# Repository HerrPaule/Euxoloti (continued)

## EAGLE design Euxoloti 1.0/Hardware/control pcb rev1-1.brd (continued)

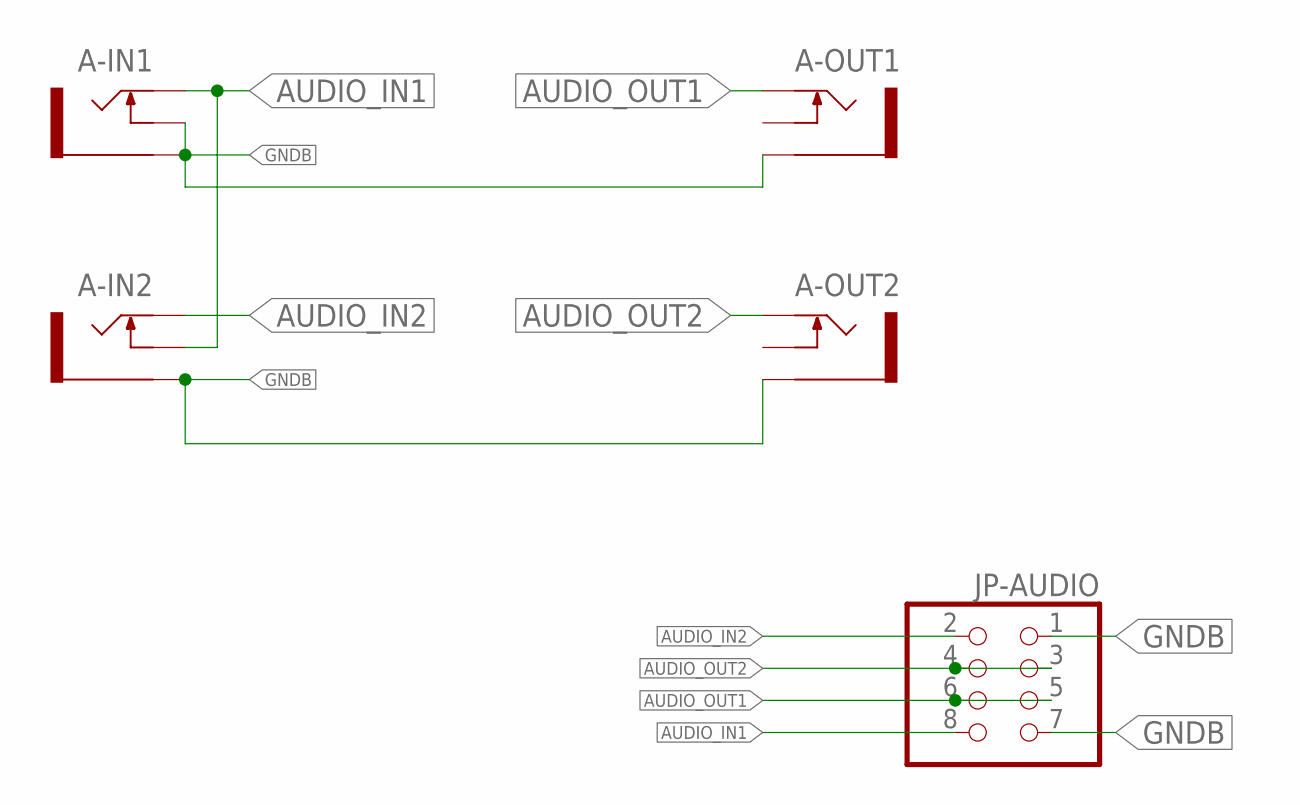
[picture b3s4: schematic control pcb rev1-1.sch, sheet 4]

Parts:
A-IN1, A-IN2: THONKICONNNEW; WQP-PJ301M-12_JACK
A-OUT1, A-OUT2: THONKICONNNEW; WQP-PJ301M-12_JACK
JP-AUDIO: PINHD-2X4_2.54; 2X04

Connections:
AUDIO_IN1: A-IN1.P$1_TIP (TIP), A-IN2.P$2_SWITCH (SWITCH), JP-AUDIO.8
AUDIO_IN2: A-IN2.P$1_TIP (TIP), JP-AUDIO.2
AUDIO_OUT1: A-OUT1.P$1_TIP (TIP), JP-AUDIO.5, JP-AUDIO.6
AUDIO_OUT2: A-OUT2.P$1_TIP (TIP), JP-AUDIO.3, JP-AUDIO.4
GNDB: A-IN1.P$2_SWITCH (SWITCH), A-IN1.P$3_SLEEVE (SLEEVE), A-IN2.P$3_SLEEVE (SLEEVE), A-OUT1.P$3_SLEEVE (SLEEVE), A-OUT2.P$3_SLEEVE (SLEEVE), JP-AUDIO.1, JP-AUDIO.7

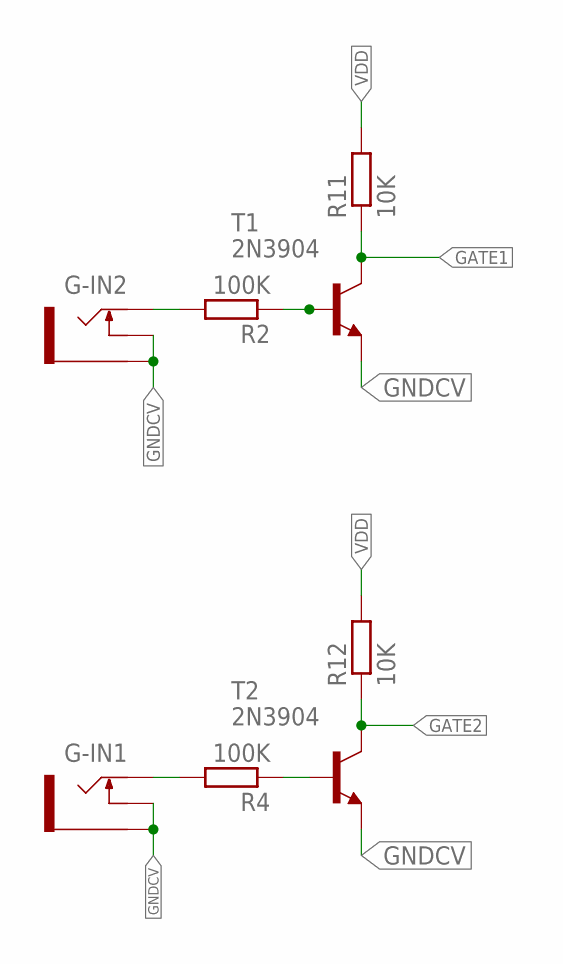
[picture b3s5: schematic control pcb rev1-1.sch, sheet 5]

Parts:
G-IN1, G-IN2: THONKICONNNEW; WQP-PJ301M-12_JACK
R2, R4: 100K; 0207/7
R11, R12: 10K; 0207/7
T1, T2: 2N3904; TO92

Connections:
GATE1: R11.1, T1.1 (C); also elsewhere on the board
GATE2: R12.1, T2.1 (C); also elsewhere on the board
GNDCV: G-IN1.P$2_SWITCH (SWITCH), G-IN1.P$3_SLEEVE (SLEEVE), G-IN2.P$2_SWITCH (SWITCH), G-IN2.P$3_SLEEVE (SLEEVE), T1.3 (E), T2.3 (E); also elsewhere on the board
unnamed: G-IN2.P$1_TIP (TIP), R2.2
unnamed: G-IN1.P$1_TIP (TIP), R4.2
unnamed: R2.1, T1.2 (B)
unnamed: R4.1, T2.2 (B)
VDD: R11.2, R12.2; also elsewhere on the board

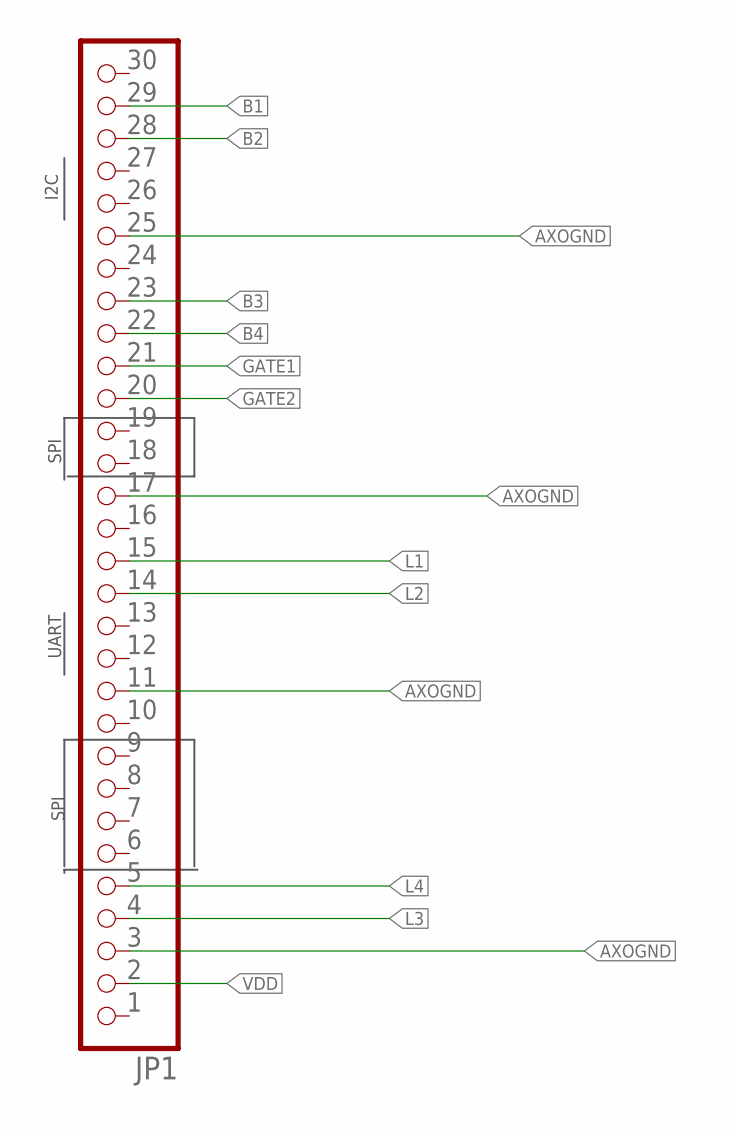
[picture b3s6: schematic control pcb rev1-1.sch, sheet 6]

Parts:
JP1: PINHD-1X30; 1X30

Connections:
AXOGND: JP1.3, JP1.11, JP1.17, JP1.25; also elsewhere on the board
B1: JP1.29; also elsewhere on the board
B2: JP1.28; also elsewhere on the board
B3: JP1.23; also elsewhere on the board
B4: JP1.22; also elsewhere on the board
GATE1: JP1.21; also elsewhere on the board
GATE2: JP1.20; also elsewhere on the board
L1: JP1.15; also elsewhere on the board
L2: JP1.14; also elsewhere on the board
L3: JP1.4; also elsewhere on the board
L4: JP1.5; also elsewhere on the board
VDD: JP1.2; also elsewhere on the board

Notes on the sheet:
SPI
UART
I2C

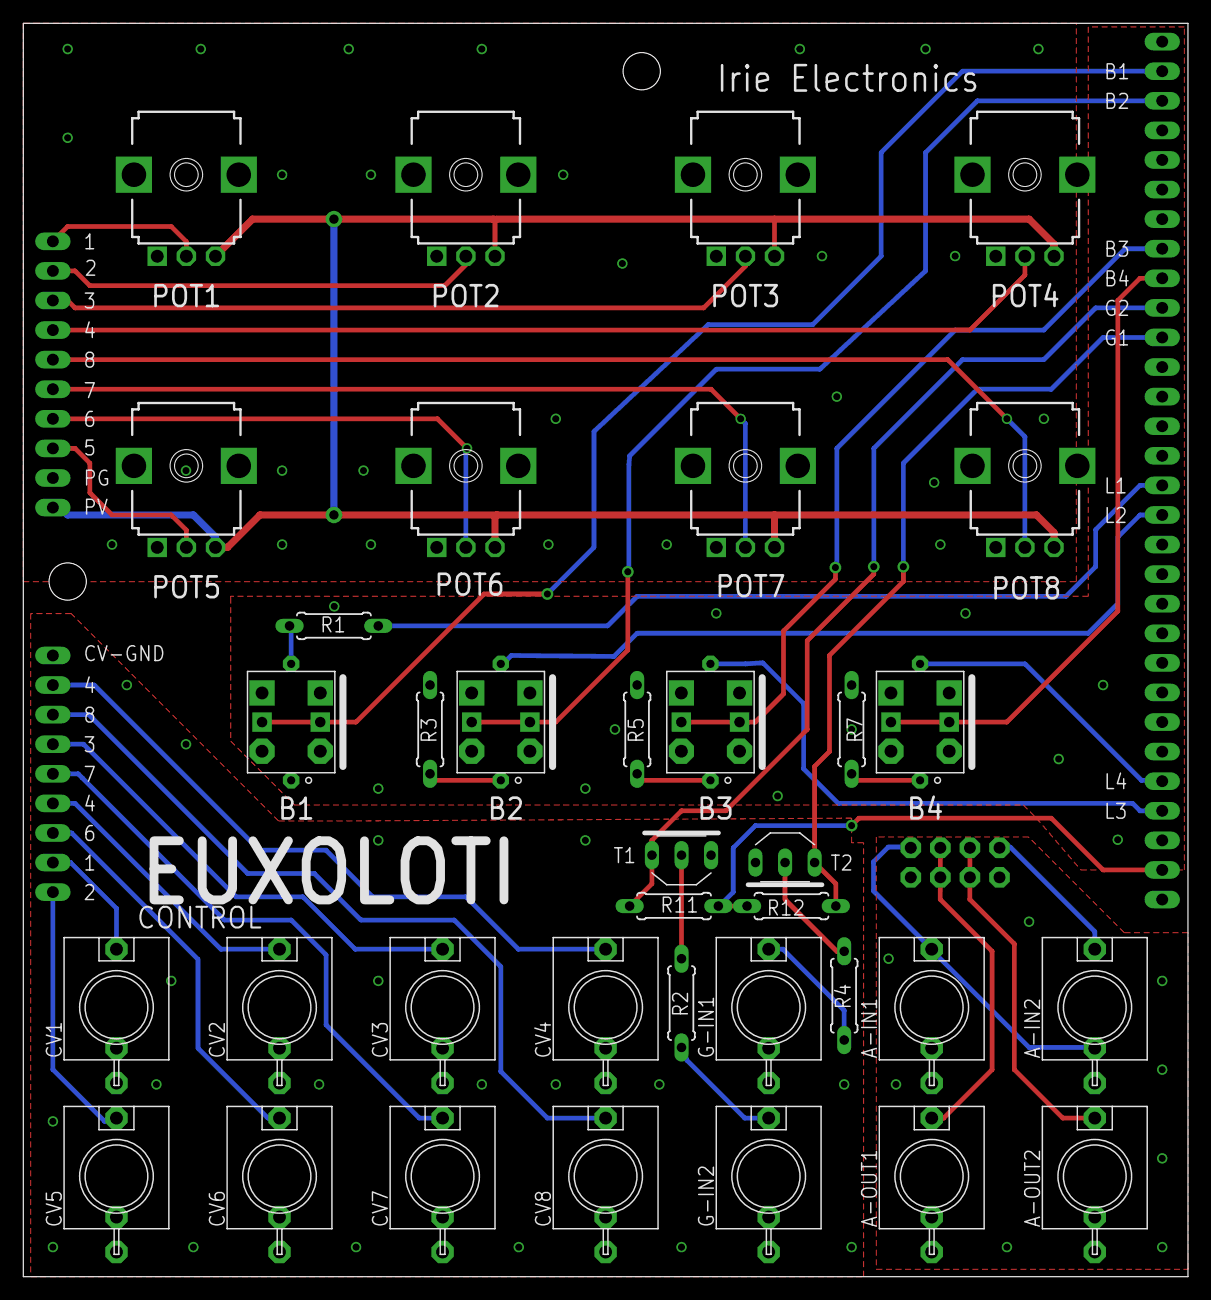
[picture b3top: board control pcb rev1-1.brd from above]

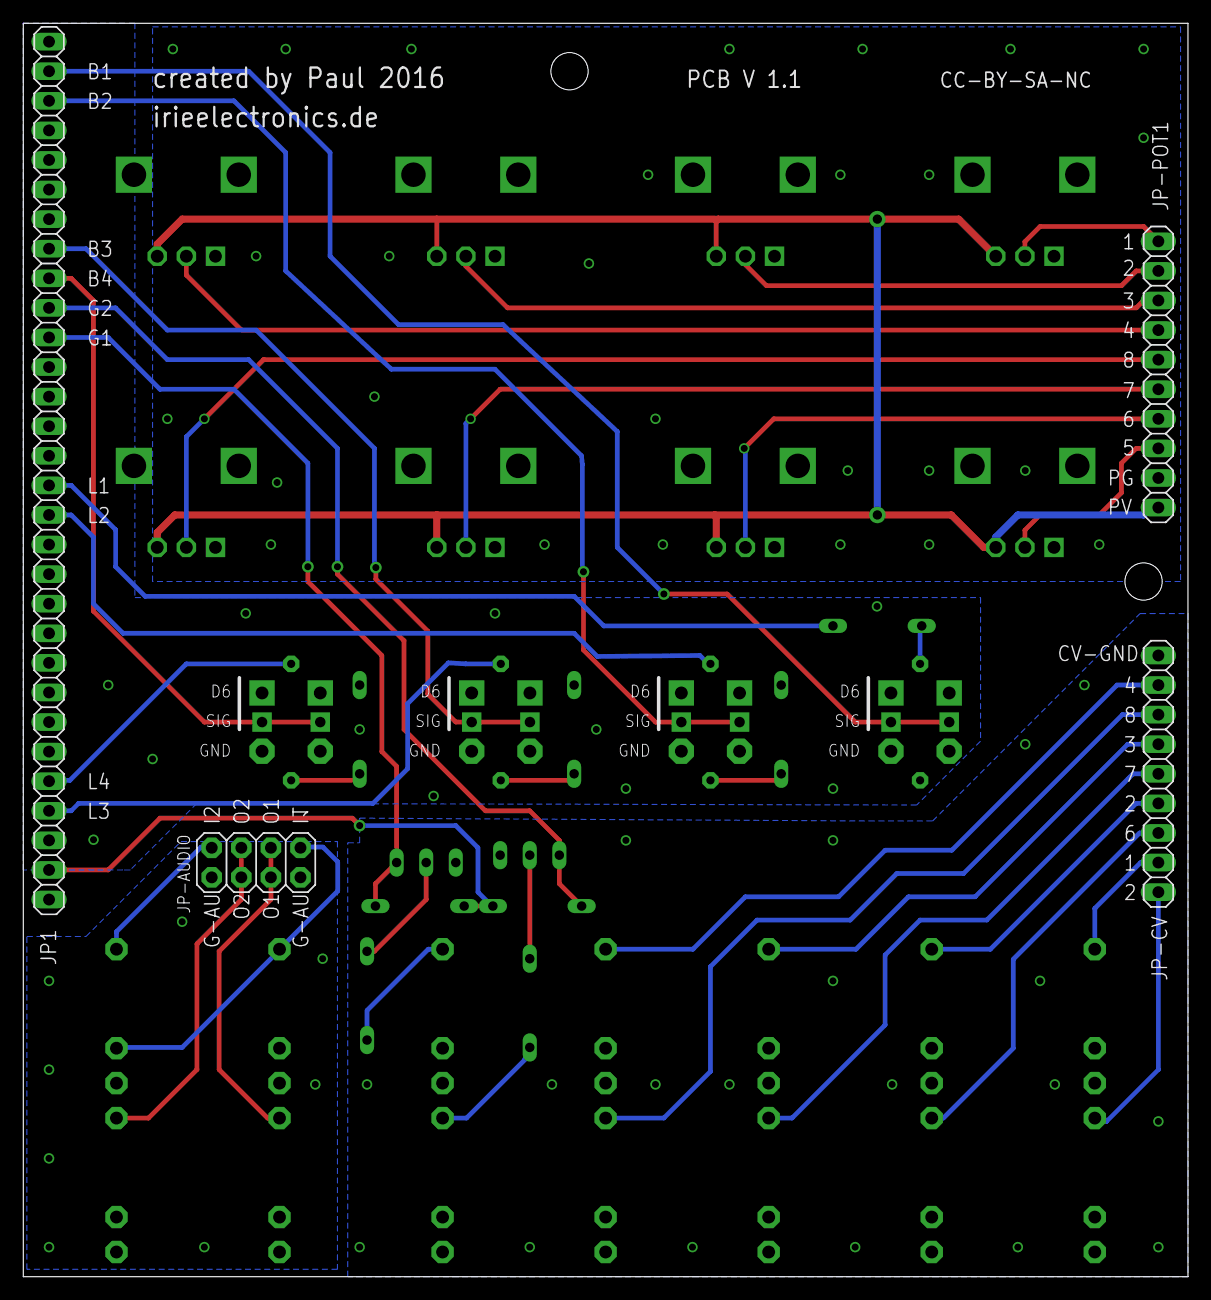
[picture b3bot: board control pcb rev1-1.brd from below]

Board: 4 copper layers, 100.0 x 107.6 mm, 40 parts (4 on the bottom side), 44 nets.

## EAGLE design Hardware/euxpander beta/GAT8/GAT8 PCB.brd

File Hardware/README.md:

##### Changelog

####### Core PCB Version 1.1:
- error correction 
- some components are rearranged or deleted
- Analog ground for ADCs, POTs and AUDIO
- better heat management for Vreg (PCB can be used as heat sink or a heatsink for TO-220)
- CS pins from ADCs are connected to other Axo pinouts
- detailed labels for pin outs and used pins.
- connections to connect upcoming "GAT8" and "USB2MCV" extensions. 
- optional use of lin/rin pins for audio directly or normalize the Eurorack signal by a big audio jack to the audio input header behind Axo's audio in jack. so you can use mics etc. like normal with Axoloti) 

####### Control PCB Version 1.1:
- larger PCB height to connect the bottom Thonkiconn jack row directly to the PCB
- single ground pins (AGND/DGND) for CV IN/GATE, POT, AUDIO I/O and pushbutton/led GND
- footprint is for LP4OA1PBCTG or D6 switches
- LEDs are now connected to PWM outputs
- Pot orientation is compatible to d-shaft type pots

####### New:
PCB Panels for Control, GAT8 and USB2MCV

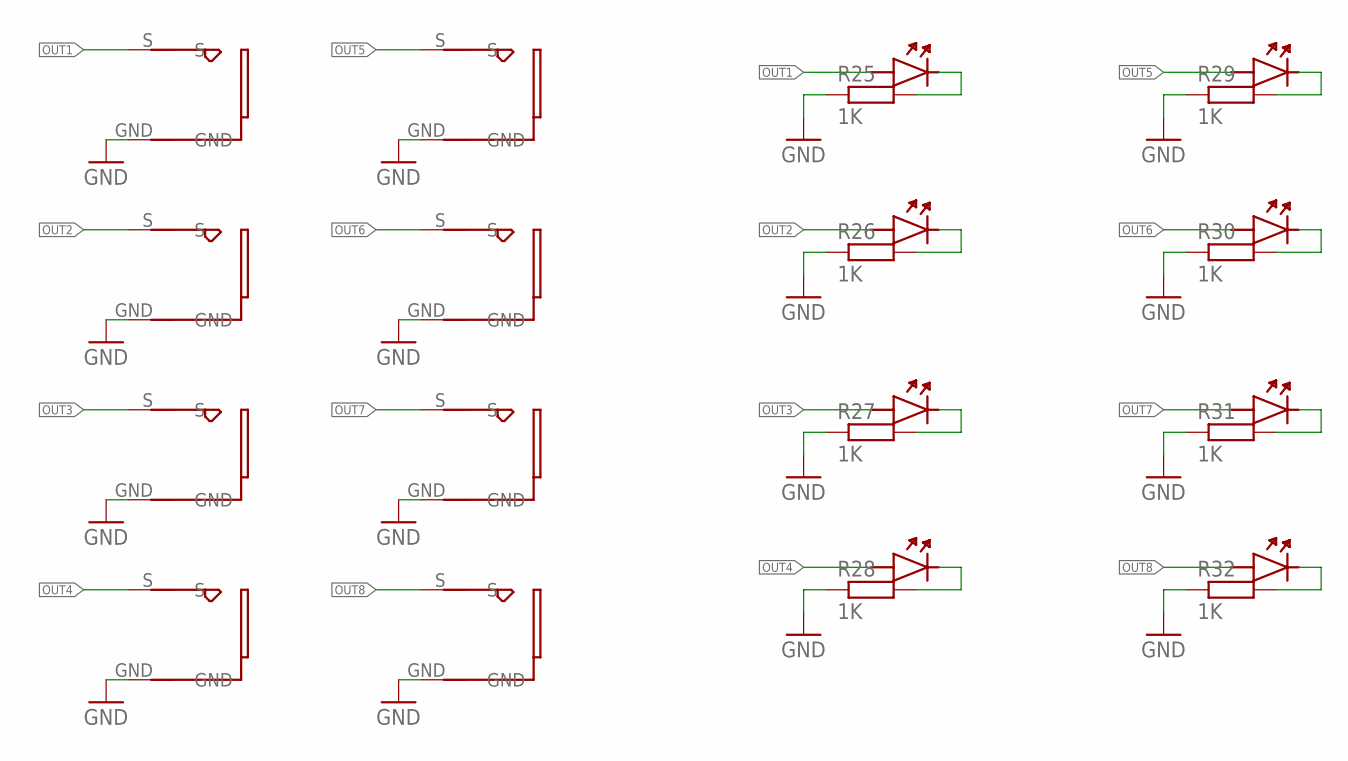
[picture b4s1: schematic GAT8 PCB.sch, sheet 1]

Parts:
LED8: LED
OUT1, OUT2, OUT3, OUT4, OUT5, OUT6, OUT7, OUT8: PJ302M
R25, R26, R27, R28, R29, R30, R31, R32: 1K; R1206
U$1, U$2, U$3, U$4, U$5, U$6, U$7: LED

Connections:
GND: OUT1.GND, OUT2.GND, OUT3.GND, OUT4.GND, OUT5.GND, OUT6.GND, OUT7.GND, OUT8.GND, R25.1, R26.1, R27.1, R28.1, R29.1, R30.1, R31.1, R32.1; also elsewhere on the board
unnamed: R26.2, U$2.GND
unnamed: R25.2, U$1.GND
unnamed: R27.2, U$3.GND
unnamed: R28.2, U$4.GND
unnamed: LED8.GND, R32.2
unnamed: R31.2, U$7.GND
unnamed: R30.2, U$6.GND
unnamed: R29.2, U$5.GND
OUT1: OUT1.S, U$1.S; also elsewhere on the board
OUT2: OUT2.S, U$2.S; also elsewhere on the board
OUT3: OUT3.S, U$3.S; also elsewhere on the board
OUT4: OUT4.S, U$4.S; also elsewhere on the board
OUT5: OUT5.S, U$5.S; also elsewhere on the board
OUT6: OUT6.S, U$6.S; also elsewhere on the board
OUT7: OUT7.S, U$7.S; also elsewhere on the board
OUT8: LED8.S, OUT8.S; also elsewhere on the board

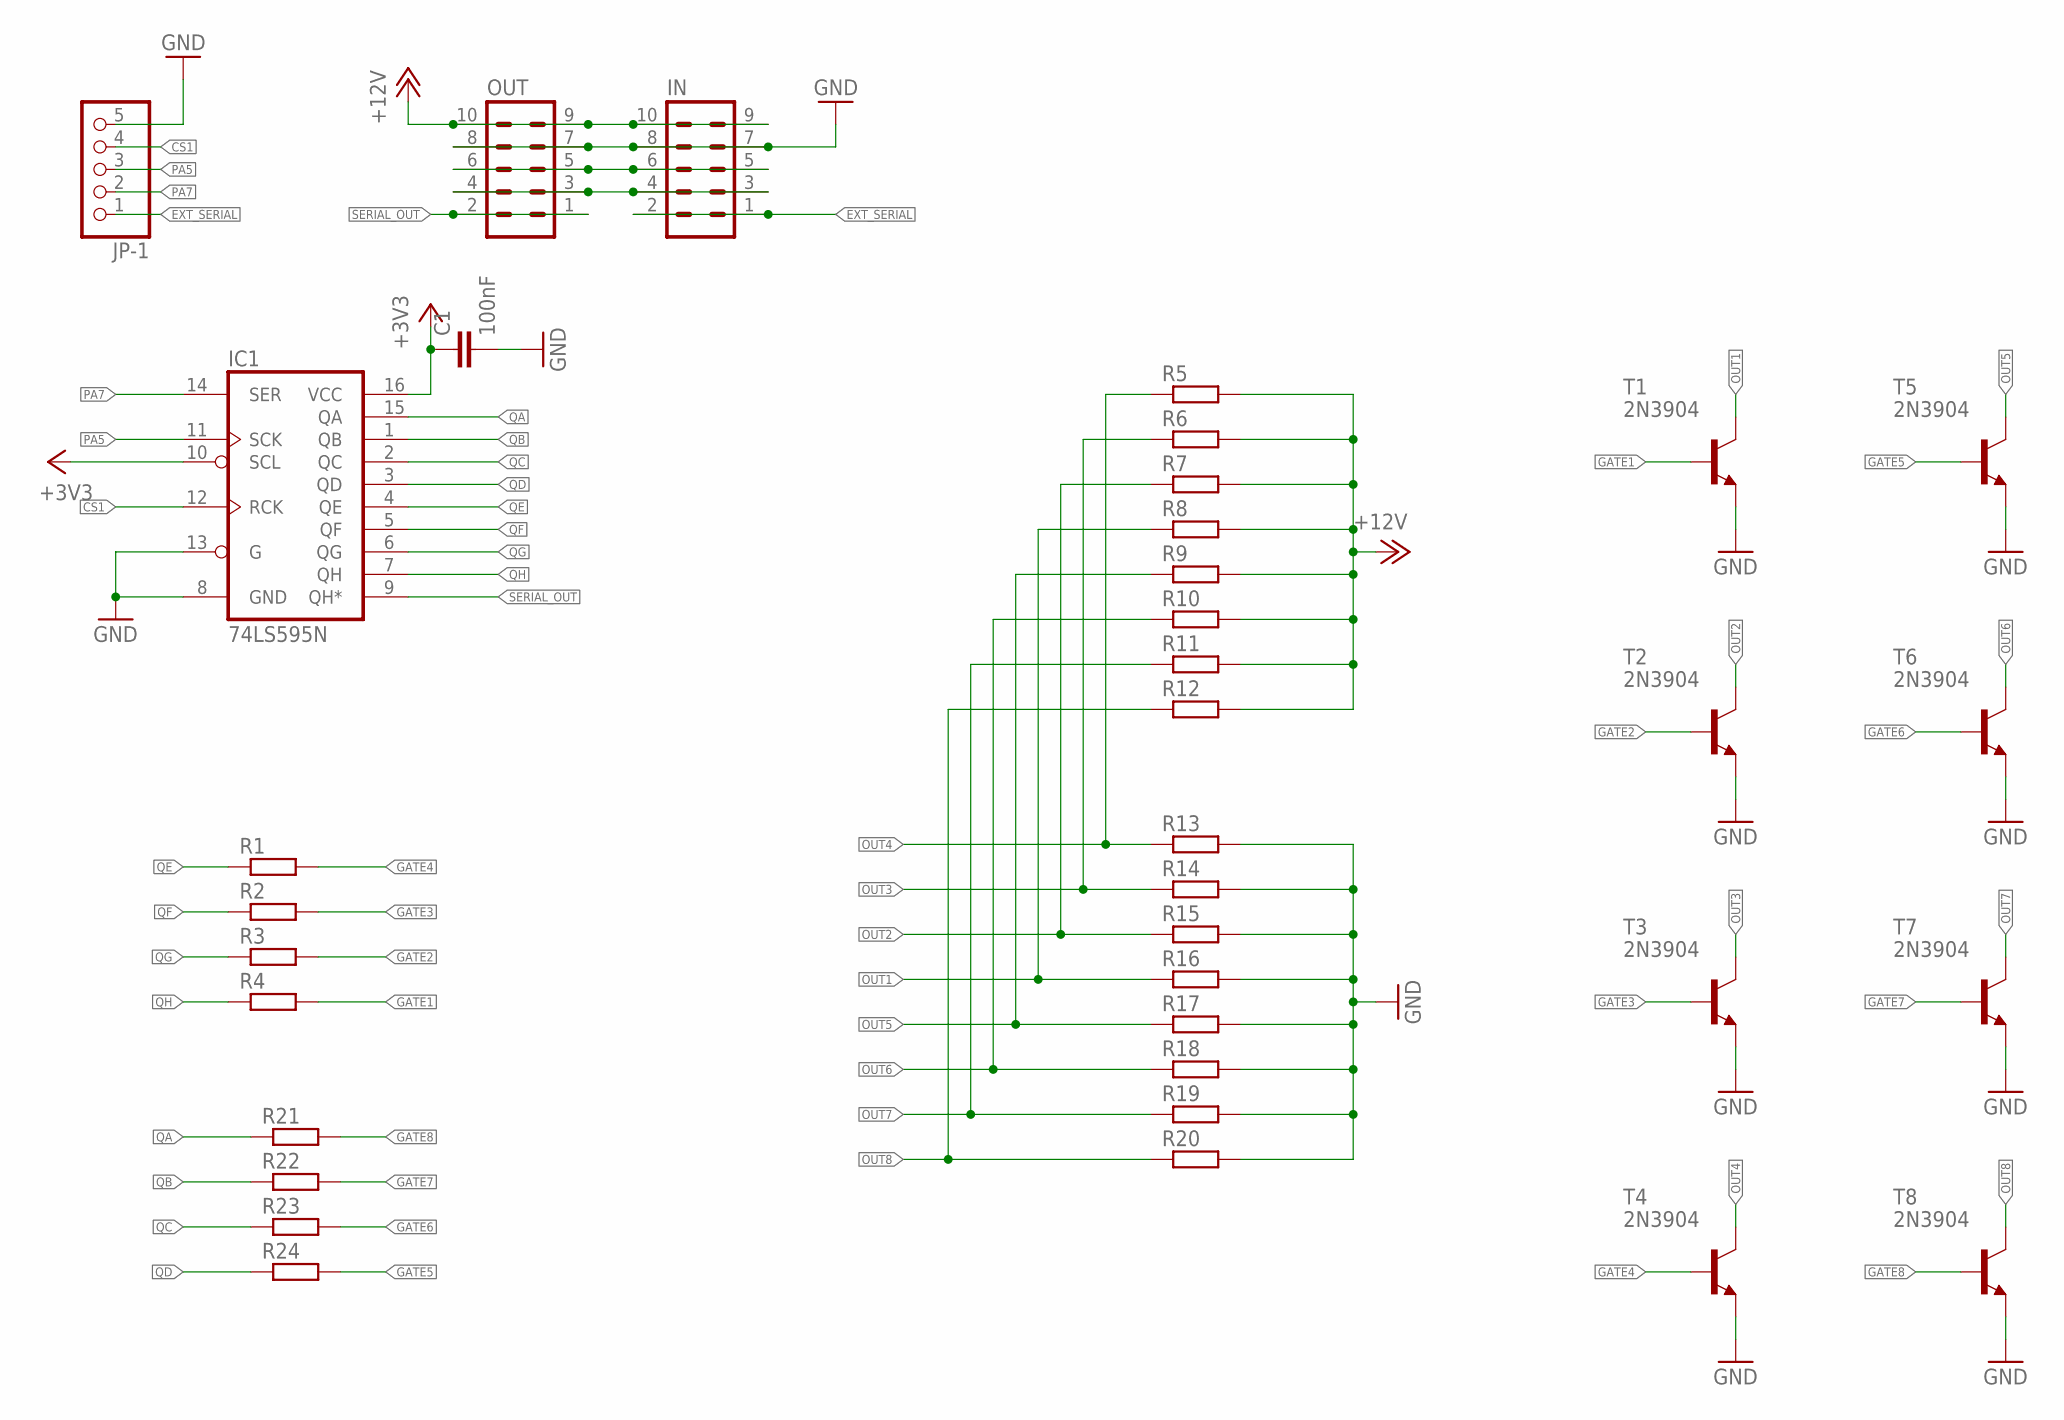
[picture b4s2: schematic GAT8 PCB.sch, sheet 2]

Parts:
C1: 100nF; C1206K
IC1: 74LS595N; DIL16
IN: ML10
JP-1: PINHD-1X5_2.54; 1X05
OUT: ML10
R1, R2, R3, R4, R5, R6, R7, R8, R9, R10, R11, R12, R13, R14, R15, R16, R17, R18, R19, R20, R21, R22, R23, R24: R-EU_R1206; R1206
T1, T2, T3, T4, T5, T6, T7, T8: 2N3904; TO92

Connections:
+3V3: C1.1, IC1.10 (SCL), IC1.16 (VCC); also elsewhere on the board
+12V: IN.9, IN.10, OUT.9, OUT.10, R5.2, R6.2, R7.2, R8.2, R9.2, R10.2, R11.2, R12.2; also elsewhere on the board
CS1: IC1.12 (RCK), JP-1.4
EXT_SERIAL: IN.1, IN.2, JP-1.1
GATE1: R4.2, T1.2 (B)
GATE2: R3.2, T2.2 (B)
GATE3: R2.2, T3.2 (B)
GATE4: R1.2, T4.2 (B)
GATE5: R24.2, T5.2 (B)
GATE6: R23.2, T6.2 (B)
GATE7: R22.2, T7.2 (B)
GATE8: R21.2, T8.2 (B)
GND: C1.2, IC1.8 (GND), IC1.13 (G), IN.7, IN.8, JP-1.5, OUT.7, OUT.8, R13.2, R14.2, R15.2, R16.2, R17.2, R18.2, R19.2, R20.2, T1.3 (E), T2.3 (E), T3.3 (E), T4.3 (E), T5.3 (E), T6.3 (E), T7.3 (E), T8.3 (E); also elsewhere on the board
unnamed: IN.3, IN.4, OUT.3, OUT.4
unnamed: IN.5, IN.6, OUT.5, OUT.6
OUT1: R8.1, R16.1, T1.1 (C); also elsewhere on the board
OUT2: R7.1, R15.1, T2.1 (C); also elsewhere on the board
OUT3: R6.1, R14.1, T3.1 (C); also elsewhere on the board
OUT4: R5.1, R13.1, T4.1 (C); also elsewhere on the board
OUT5: R9.1, R17.1, T5.1 (C); also elsewhere on the board
OUT6: R10.1, R18.1, T6.1 (C); also elsewhere on the board
OUT7: R11.1, R19.1, T7.1 (C); also elsewhere on the board
OUT8: R12.1, R20.1, T8.1 (C); also elsewhere on the board
PA5: IC1.11 (SCK), JP-1.3
PA7: IC1.14 (SER), JP-1.2
QA: IC1.15 (QA), R21.1
QB: IC1.1 (QB), R22.1
QC: IC1.2 (QC), R23.1
QD: IC1.3 (QD), R24.1
QE: IC1.4 (QE), R1.1
QF: IC1.5 (QF), R2.1
QG: IC1.6 (QG), R3.1
QH: IC1.7 (QH), R4.1
SERIAL_OUT: IC1.9 (QH*), OUT.1, OUT.2

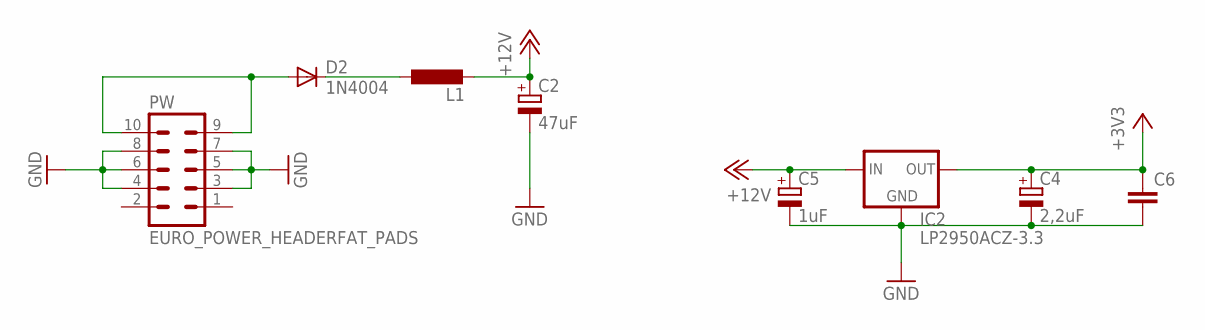
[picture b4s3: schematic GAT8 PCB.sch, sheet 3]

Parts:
C2: 47uF; E2-5
C4: 2,2uF; E2-5
C5: 1uF; E2-5
C6: C-EUC1206K; C1206K
D2: 1N4004; DO41-10
IC2: LP2950ACZ-3.3; TO92
L1: L-EU0207/10; 0207/10
PW: EURO_POWER_HEADERFAT_PADS; EURO_PWR_HEADER_FAT

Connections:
+3V3: C4.+, C6.1, IC2.1 (OUT); also elsewhere on the board
+12V: C2.+, C5.+, IC2.3 (IN), L1.2; also elsewhere on the board
GND: C2.-, C4.-, C5.-, C6.2, IC2.2 (GND), PW.3, PW.4, PW.5, PW.6, PW.7, PW.8; also elsewhere on the board
unnamed: D2.A, PW.9, PW.10
unnamed: D2.C, L1.1

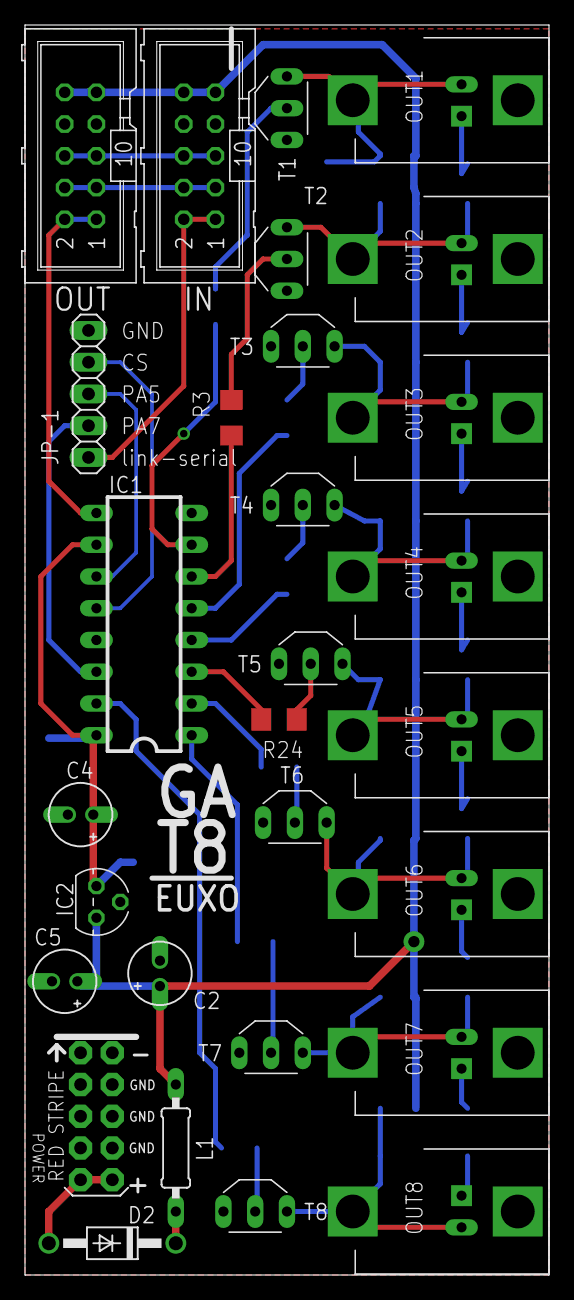
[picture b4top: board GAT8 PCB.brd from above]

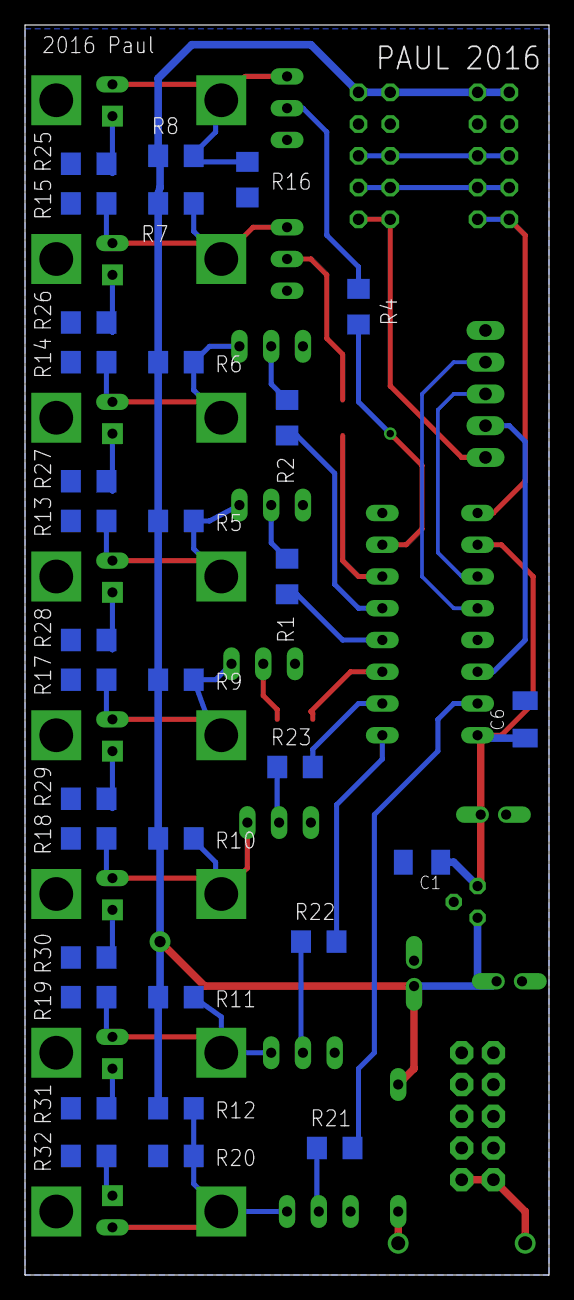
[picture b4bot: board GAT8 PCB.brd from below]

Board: 2 copper layers, 41.9 x 100.0 mm, 69 parts (40 on the bottom side), 44 nets.

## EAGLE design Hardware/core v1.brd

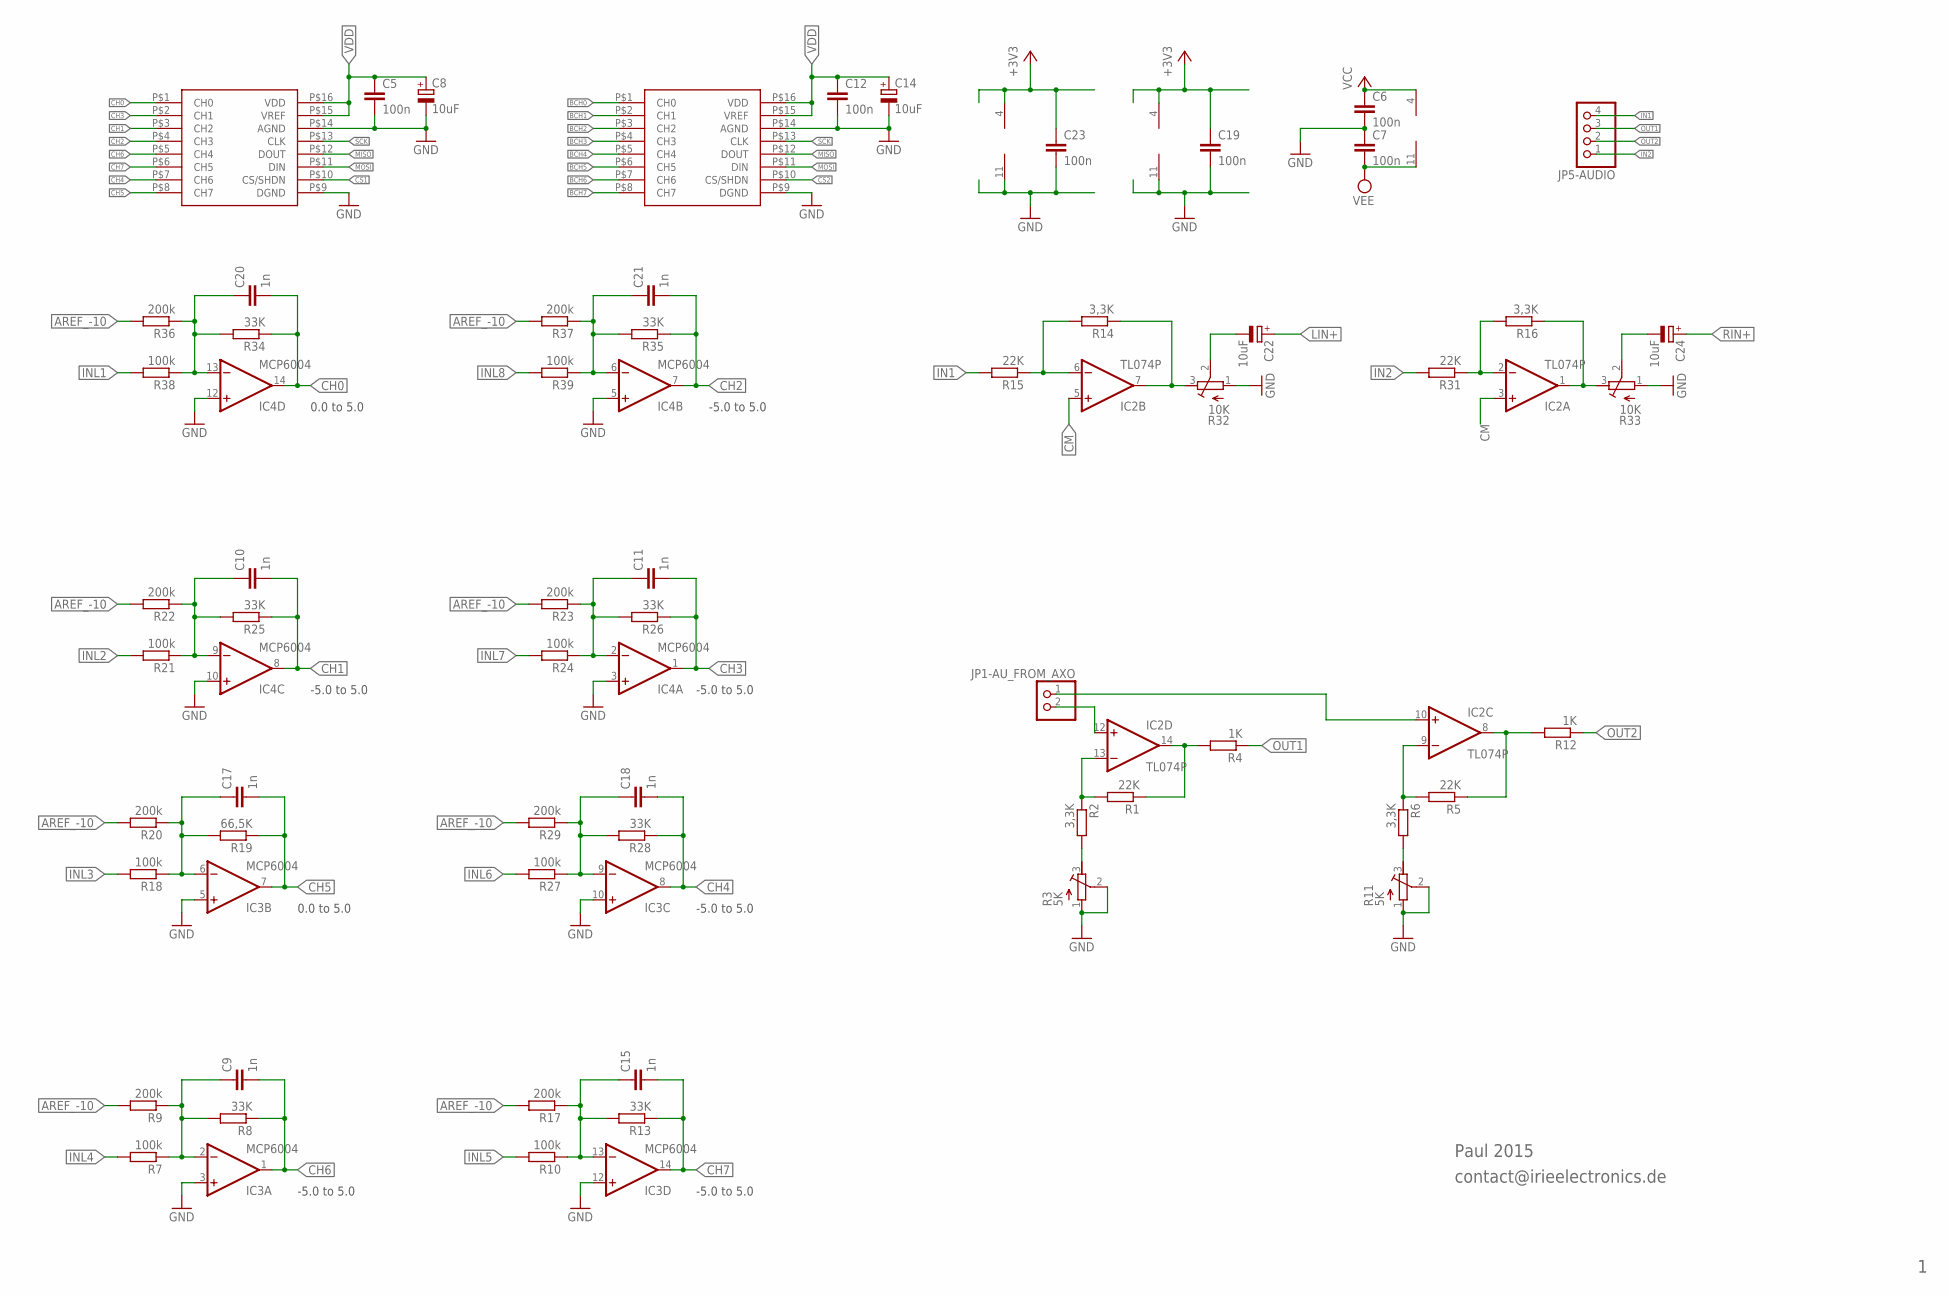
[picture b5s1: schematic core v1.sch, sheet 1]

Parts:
C5, C6, C7, C12, C19, C23: 100n; C025-025X050
C8, C14, C22, C24: 10uF; E1,8-4
C9, C10, C11, C15, C17, C18, C20, C21: 1n; C050-025X075
IC2: TL074P; DIL14
IC3, IC4: MCP6004; DIL14
JP1-AU_FROM_AXO: PINHD-1X2/90; 1X02/90
JP5-AUDIO: PINHD-1X4_2.54; 1X04
R1: 22K; 0207/10
R2: 3,3K; 0207/12
R3, R11: 5K; RTRIM3296P
R4: 1K; 0207/7
R5, R15, R31: 22K; 0207/7
R6, R14, R16: 3,3K; 0207/7
R7, R10, R18, R21, R27, R38, R39: 100k; 0207/7
R8, R13, R25, R26, R28, R34, R35: 33K; 0207/7
R9, R20: 200k; 0207/10
R12: 1K; 0207/10
R17, R22, R23, R29, R36, R37: 200k; 0207/7
R19: 66,5K; 0207/7
R24: 100k; 0207/10
R32, R33: 10K; RTRIM3296P
U$4, U$5: MCP3208_DIP; MCP2308

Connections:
+3V3: C19.1, C23.1, IC3.4 (V+), IC4.4 (V+); also elsewhere on the board
AREF_-10: R9.2, R17.2, R20.2, R22.2, R23.2, R29.2, R36.2, R37.2; also elsewhere on the board
BCH0: U$5.P$1 (CH0); also elsewhere on the board
BCH1: U$5.P$2 (CH1); also elsewhere on the board
BCH2: U$5.P$3 (CH2); also elsewhere on the board
BCH3: U$5.P$4 (CH3); also elsewhere on the board
BCH4: U$5.P$5 (CH4); also elsewhere on the board
BCH5: U$5.P$6 (CH5); also elsewhere on the board
BCH6: U$5.P$7 (CH6); also elsewhere on the board
BCH7: U$5.P$8 (CH7); also elsewhere on the board
CH0: C20.2, IC4.14 (OUT), R34.1, U$4.P$1 (CH0)
CH1: C10.2, IC4.8 (OUT), R25.1, U$4.P$3 (CH2)
CH2: C21.2, IC4.7 (OUT), R35.1, U$4.P$4 (CH3)
CH3: C11.2, IC4.1 (OUT), R26.1, U$4.P$2 (CH1)
CH4: C18.2, IC3.8 (OUT), R28.1, U$4.P$7 (CH6)
CH5: C17.2, IC3.7 (OUT), R19.1, U$4.P$8 (CH7)
CH6: C9.2, IC3.1 (OUT), R8.1, U$4.P$5 (CH4)
CH7: C15.2, IC3.14 (OUT), R13.1, U$4.P$6 (CH5)
CM: IC2.3 (+IN), IC2.5 (+IN); also elsewhere on the board
CS1: U$4.P$10 (CS/SHDN); also elsewhere on the board
CS2: U$5.P$10 (CS/SHDN); also elsewhere on the board
GND: C5.2, C6.2, C7.1, C8.-, C12.2, C14.-, C19.2, C23.2, IC3.3 (+IN), IC3.5 (+IN), IC3.10 (+IN), IC3.11 (V-), IC3.12 (+IN), IC4.3 (+IN), IC4.5 (+IN), IC4.10 (+IN), IC4.11 (V-), IC4.12 (+IN), R3.1 (E), R3.2 (S), R11.1 (E), R11.2 (S), R32.1 (E), R33.1 (E), U$4.P$9 (DGND), U$4.P$14 (AGND), U$5.P$9 (DGND), U$5.P$14 (AGND); also elsewhere on the board
IN1: JP5-AUDIO.4, R15.2
IN2: JP5-AUDIO.1, R31.2
INL1: R38.2; also elsewhere on the board
INL2: R21.2; also elsewhere on the board
INL3: R18.2; also elsewhere on the board
INL4: R7.2; also elsewhere on the board
INL5: R10.2; also elsewhere on the board
INL6: R27.2; also elsewhere on the board
INL7: R24.2; also elsewhere on the board
INL8: R39.2; also elsewhere on the board
LIN+: C22.+; also elsewhere on the board
MISO: U$4.P$12 (DOUT), U$5.P$12 (DOUT); also elsewhere on the board
MOSI: U$4.P$11 (DIN), U$5.P$11 (DIN); also elsewhere on the board
unnamed: C10.1, IC4.9 (-IN), R21.1, R22.1, R25.2
unnamed: R2.2, R3.3 (A)
unnamed: C11.1, IC4.2 (-IN), R23.1, R24.1, R26.2
unnamed: IC2.13 (-IN), R1.2, R2.1
unnamed: IC2.14 (OUT), R1.1, R4.2
unnamed: C22.-, R32.2 (S)
unnamed: R6.2, R11.3 (A)
unnamed: IC2.9 (-IN), R5.2, R6.1
unnamed: C20.1, IC4.13 (-IN), R34.2, R36.1, R38.1
unnamed: IC2.8 (OUT), R5.1, R12.2
unnamed: IC2.10 (+IN), JP1-AU_FROM_AXO.1
unnamed: IC2.12 (+IN), JP1-AU_FROM_AXO.2
unnamed: C21.1, IC4.6 (-IN), R35.2, R37.1, R39.1
unnamed: C24.-, R33.2 (S)
unnamed: IC2.6 (-IN), R14.2, R15.1
unnamed: C9.1, IC3.2 (-IN), R7.1, R8.2, R9.1
unnamed: IC2.7 (OUT), R14.1, R32.3 (A)
unnamed: C15.1, IC3.13 (-IN), R10.1, R13.2, R17.1
unnamed: IC2.2 (-IN), R16.2, R31.1
unnamed: C17.1, IC3.6 (-IN), R18.1, R19.2, R20.1
unnamed: IC2.1 (OUT), R16.1, R33.3 (A)
unnamed: C18.1, IC3.9 (-IN), R27.1, R28.2, R29.1
OUT1: JP5-AUDIO.3, R4.1
OUT2: JP5-AUDIO.2, R12.1
RIN+: C24.+; also elsewhere on the board
SCK: U$4.P$13 (CLK), U$5.P$13 (CLK); also elsewhere on the board
VCC: C6.1, IC2.4 (V+); also elsewhere on the board
VDD: C5.1, C8.+, C12.1, C14.+, U$4.P$15 (VREF), U$4.P$16 (VDD), U$5.P$15 (VREF), U$5.P$16 (VDD); also elsewhere on the board
VEE: C7.2, IC2.11 (V-); also elsewhere on the board

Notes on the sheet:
-5.0 to 5.0
0.0 to 5.0
Paul 2015
contact@irieelectronics.de
